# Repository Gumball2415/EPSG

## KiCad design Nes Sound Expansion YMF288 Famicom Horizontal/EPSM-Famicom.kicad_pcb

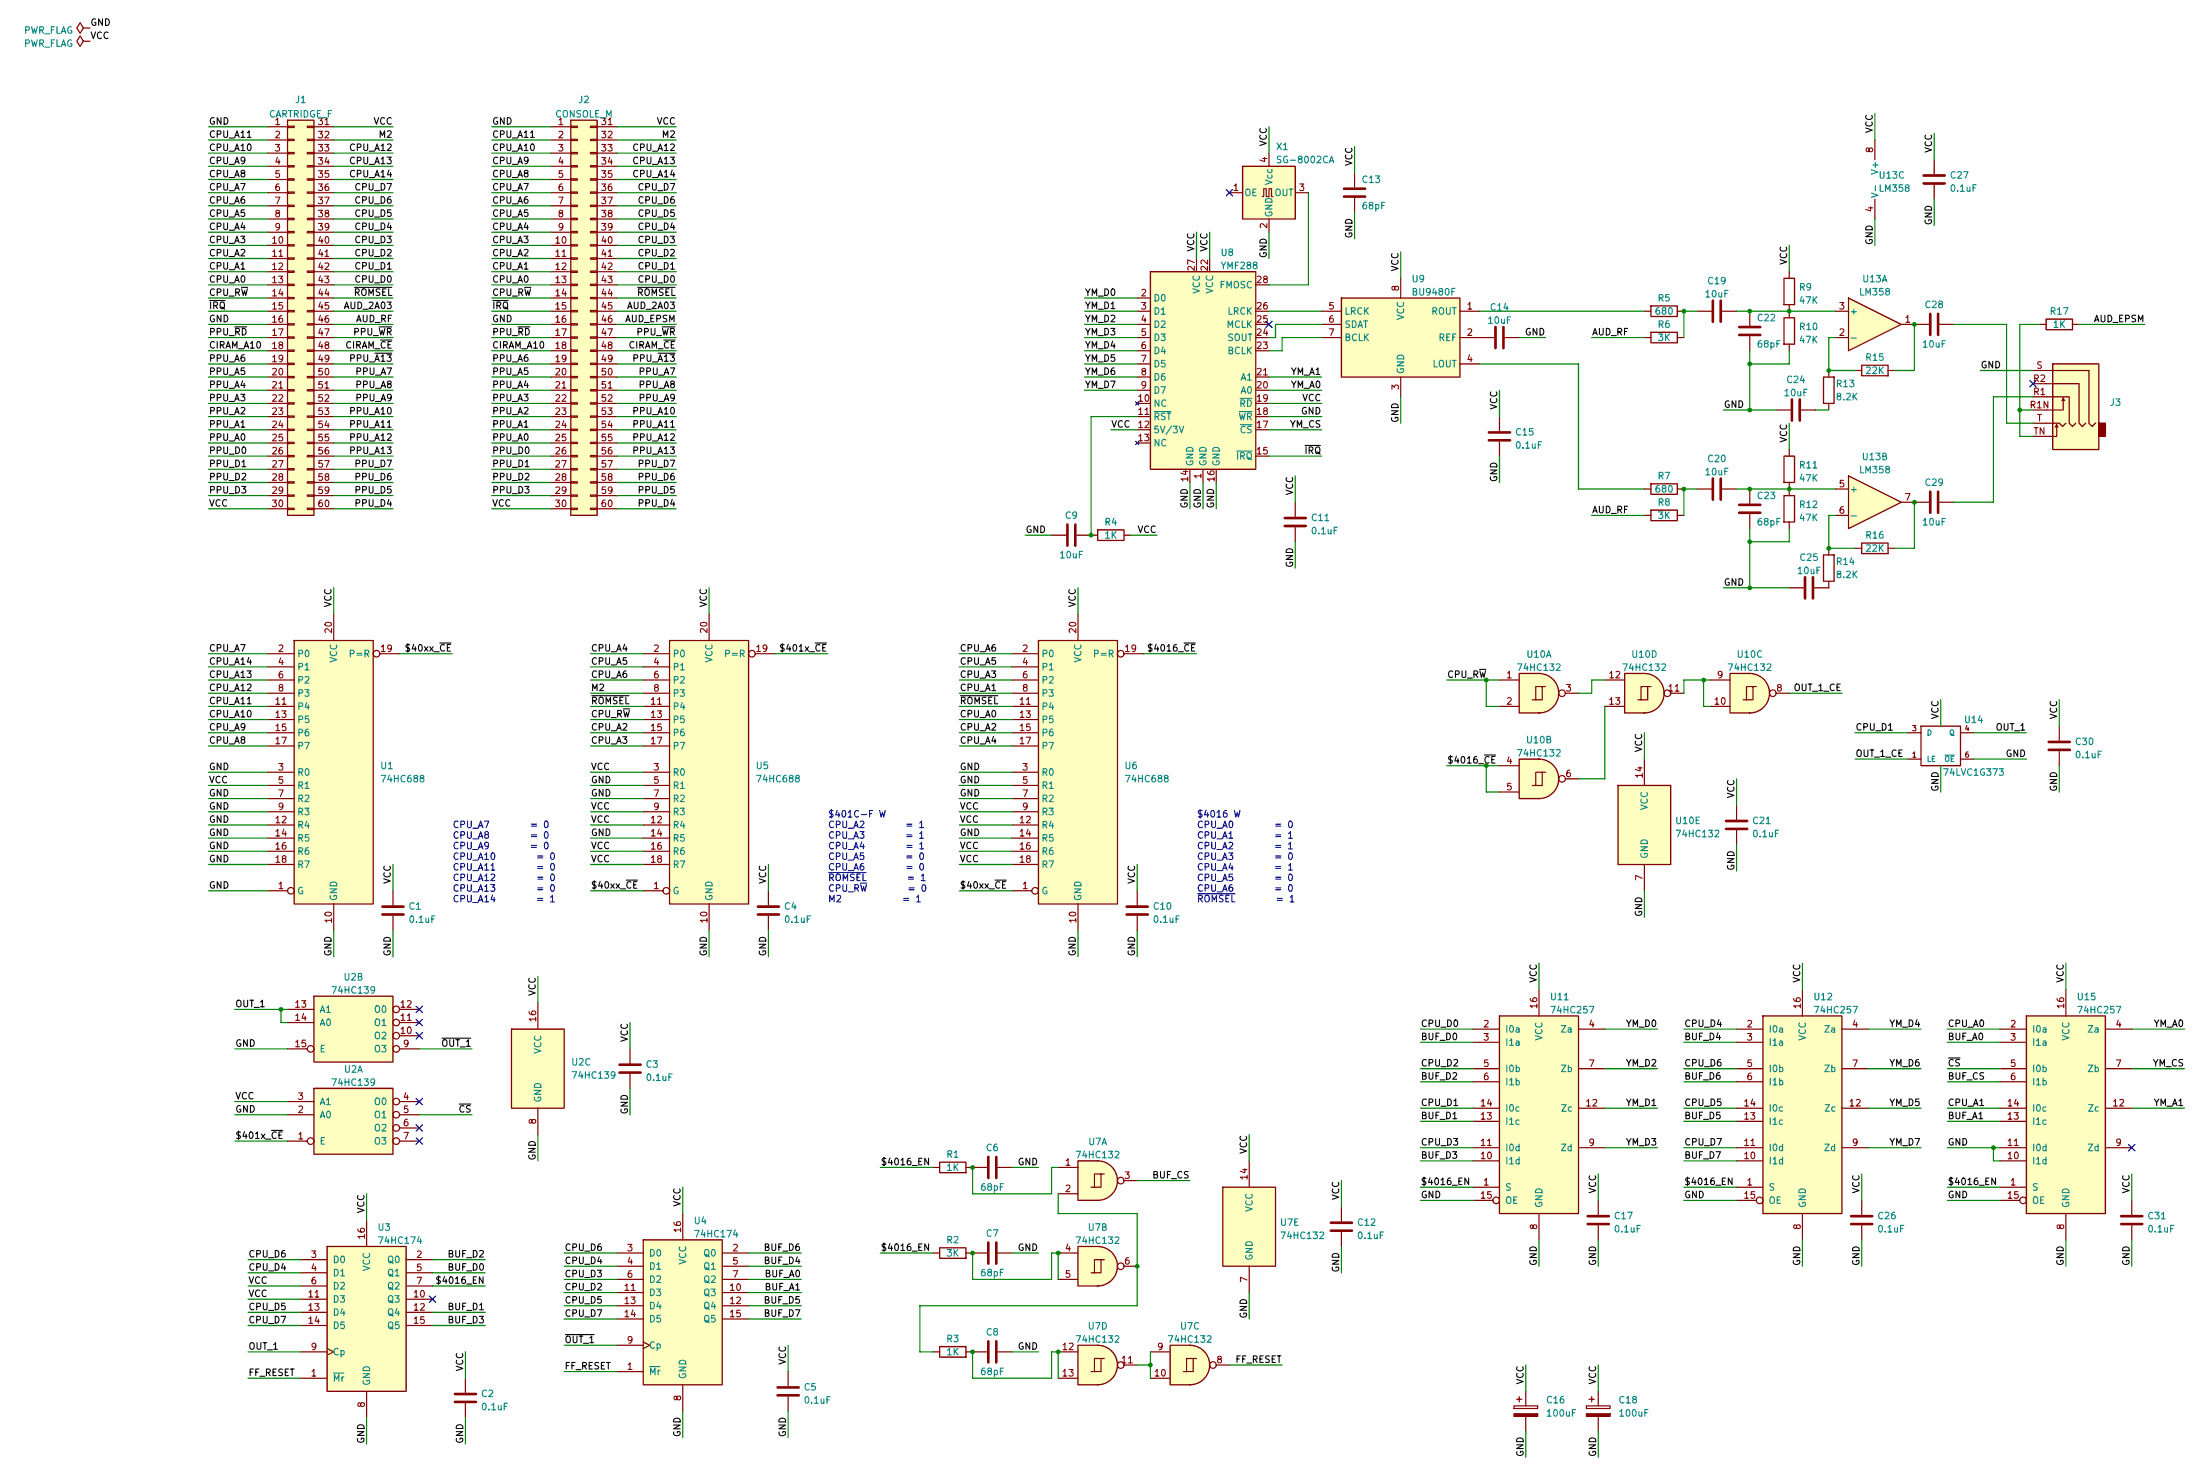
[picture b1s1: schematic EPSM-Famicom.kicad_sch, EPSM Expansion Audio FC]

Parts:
C1, C2, C3, C4, C5, C10, C11, C12, C15, C17, C21, C26, C27, C30, C31: 0.1uF; C_0805_2012Metric_Pad1.18x1.45mm_HandSolder
C6, C7, C8, C13, C22, C23: 68pF; C_0805_2012Metric_Pad1.18x1.45mm_HandSolder
C9, C14, C19, C20, C24, C25, C28, C29: 10uF; C_0805_2012Metric_Pad1.18x1.45mm_HandSolder
C16, C18: 100uF; CP_Elec_6.3x5.4
J1: CARTRIDGE_F; FC_CONN_F
J2: CONSOLE_M; HVC-ETROM-01
J3: AudioJack4_SwitchTR1; Jack_3.5mm_PJ311_Horizontal
R1, R3, R4, R17: 1K; R_0805_2012Metric_Pad1.20x1.40mm_HandSolder
R2, R6, R8: 3K; R_0805_2012Metric_Pad1.20x1.40mm_HandSolder
R5, R7: 680; R_0805_2012Metric_Pad1.20x1.40mm_HandSolder
R9, R10, R11, R12: 47K; R_0805_2012Metric_Pad1.20x1.40mm_HandSolder
R13, R14: 8.2K; R_0805_2012Metric_Pad1.20x1.40mm_HandSolder
R15, R16: 22K; R_0805_2012Metric_Pad1.20x1.40mm_HandSolder
U1, U5, U6: 74HC688; SOIC-20W_7.5x12.8mm_P1.27mm
U2: 74HC139; SOIC-16_3.9x9.9mm_P1.27mm
U3, U4: 74HC174; SOIC-16_3.9x9.9mm_P1.27mm
U7, U10: 74HC132; SOIC-14_3.9x8.7mm_P1.27mm
U8: YMF288; SOP-28_8.4x18.1mm_P1.27mm
U9: BU9480F; SOIC-8_3.9x4.9mm_P1.27mm
U11, U12, U15: 74HC257; SOIC-16_3.9x9.9mm_P1.27mm
U13: LM358; SOIC-8_3.9x4.9mm_P1.27mm
U14: 74LVC1G373; SOT-23-6
X1: SG-8002CA; Oscillator_SMD_Abracon_ASV-4Pin_7.0x5.1mm

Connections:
/$40xx_~CE: U1.19 (P=R), U5.1 (G), U6.1 (G)
/$401x_~CE: U2.1 (E), U5.19 (P=R)
/$4016_EN: R1.1, R2.1, U3.7 (Q2), U11.1 (S), U12.1 (S), U15.1 (S)
/$4016_~CE: U6.19 (P=R), U10.4, U10.5
/AUD_2A03: J1.45, J2.45
/AUD_EPSM: J2.46, R17.2
/AUD_RF: J1.46, R6.2, R8.2
/BUF_A0: U4.7 (Q2), U15.3 (I1a)
/BUF_A1: U4.10 (Q3), U15.13 (I1c)
/BUF_CS: U7.3, U15.6 (I1b)
/BUF_D0: U3.5 (Q1), U11.3 (I1a)
/BUF_D1: U3.12 (Q4), U11.13 (I1c)
/BUF_D2: U3.2 (Q0), U11.6 (I1b)
/BUF_D3: U3.15 (Q5), U11.10 (I1d)
/BUF_D4: U4.5 (Q1), U12.3 (I1a)
/BUF_D5: U4.12 (Q4), U12.13 (I1c)
/BUF_D6: U4.2 (Q0), U12.6 (I1b)
/BUF_D7: U4.15 (Q5), U12.10 (I1d)
/CIRAM_A10: J1.18, J2.18
/CIRAM_~CE: J1.48, J2.48
/CPU_A0: J1.13, J2.13, U6.13 (P5), U15.2 (I0a)
/CPU_A1: J1.12, J2.12, U6.8 (P3), U15.14 (I0c)
/CPU_A2: J1.11, J2.11, U5.15 (P6), U6.15 (P6)
/CPU_A3: J1.10, J2.10, U5.17 (P7), U6.6 (P2)
/CPU_A4: J1.9, J2.9, U5.2 (P0), U6.17 (P7)
/CPU_A5: J1.8, J2.8, U5.4 (P1), U6.4 (P1)
/CPU_A6: J1.7, J2.7, U5.6 (P2), U6.2 (P0)
/CPU_A7: J1.6, J2.6, U1.2 (P0)
/CPU_A8: J1.5, J2.5, U1.17 (P7)
/CPU_A9: J1.4, J2.4, U1.15 (P6)
/CPU_A10: J1.3, J2.3, U1.13 (P5)
/CPU_A11: J1.2, J2.2, U1.11 (P4)
/CPU_A12: J1.33, J2.33, U1.8 (P3)
/CPU_A13: J1.34, J2.34, U1.6 (P2)
/CPU_A14: J1.35, J2.35, U1.4 (P1)
/CPU_D0: J1.43, J2.43, U11.2 (I0a)
/CPU_D1: J1.42, J2.42, U11.14 (I0c), U14.3 (D)
/CPU_D2: J1.41, J2.41, U4.11 (D3), U11.5 (I0b)
/CPU_D3: J1.40, J2.40, U4.6 (D2), U11.11 (I0d)
/CPU_D4: J1.39, J2.39, U3.4 (D1), U4.4 (D1), U12.2 (I0a)
/CPU_D5: J1.38, J2.38, U3.13 (D4), U4.13 (D4), U12.14 (I0c)
/CPU_D6: J1.37, J2.37, U3.3 (D0), U4.3 (D0), U12.5 (I0b)
/CPU_D7: J1.36, J2.36, U3.14 (D5), U4.14 (D5), U12.11 (I0d)
/CPU_R~W: J1.14, J2.14, U5.13 (P5), U10.1, U10.2
/FF_RESET: U3.1 (~Mr), U4.1 (~Mr), U7.8
/M2: J1.32, J2.32, U5.8 (P3)
/OUT_1: U2.13 (A1), U2.14 (A0), U3.9 (Cp), U14.4 (Q)
/OUT_1_CE: U10.8, U14.1 (LE)
/PPU_A0: J1.25, J2.25
/PPU_A1: J1.24, J2.24
/PPU_A2: J1.23, J2.23
/PPU_A3: J1.22, J2.22
/PPU_A4: J1.21, J2.21
/PPU_A5: J1.20, J2.20
/PPU_A6: J1.19, J2.19
/PPU_A7: J1.50, J2.50
/PPU_A8: J1.51, J2.51
/PPU_A9: J1.52, J2.52
/PPU_A10: J1.53, J2.53
/PPU_A11: J1.54, J2.54
/PPU_A12: J1.55, J2.55
/PPU_A13: J1.56, J2.56
/PPU_D0: J1.26, J2.26
/PPU_D1: J1.27, J2.27
/PPU_D2: J1.28, J2.28
/PPU_D3: J1.29, J2.29
/PPU_D4: J1.60, J2.60
/PPU_D5: J1.59, J2.59
/PPU_D6: J1.58, J2.58
/PPU_D7: J1.57, J2.57
/PPU_~A13: J1.49, J2.49
/PPU_~RD: J1.17, J2.17
/PPU_~WR: J1.47, J2.47
/YM_A0: U8.20 (A0), U15.4 (Za)
/YM_A1: U8.21 (A1), U15.12 (Zc)
/YM_CS: U8.17 (~CS), U15.7 (Zb)
/YM_D0: U8.2 (D0), U11.4 (Za)
/YM_D1: U8.3 (D1), U11.12 (Zc)
/YM_D2: U8.4 (D2), U11.7 (Zb)
/YM_D3: U8.5 (D3), U11.9 (Zd)
/YM_D4: U8.6 (D4), U12.4 (Za)
/YM_D5: U8.7 (D5), U12.12 (Zc)
/YM_D6: U8.8 (D6), U12.7 (Zb)
/YM_D7: U8.9 (D7), U12.9 (Zd)
/~CS: U2.5 (O1), U15.5 (I0b)
/~IRQ: J1.15, J2.15, U8.15 (~IRQ)
/~OUT_1: U2.9 (O3), U4.9 (Cp)
/~ROMSEL: J1.44, J2.44, U5.11 (P4), U6.11 (P4)
GND: C1.1, C2.1, C3.1, C4.1, C5.1, C6.2, C7.2, C8.2, C9.1, C10.1, C11.1, C12.1, C13.2, C14.2, C15.1, C16.2, C17.1, C18.2, C21.1, C22.2, C23.2, C24.1, C25.1, C26.1, C27.1, C30.1, C31.1, J1.1, J1.16, J2.1, J2.16, J3.S, R10.2, R12.2, U1.1 (G), U1.3 (R0), U1.7 (R2), U1.9 (R3), U1.10 (GND), U1.12 (R4), U1.14 (R5), U1.16 (R6), U1.18 (R7), U2.2 (A0), U2.8 (GND), U2.15 (E), U3.8 (GND), U4.8 (GND), U5.5 (R1), U5.7 (R2), U5.10 (GND), U5.14 (R5), U6.3 (R0), U6.5 (R1), U6.7 (R2), U6.10 (GND), U6.14 (R5), U7.7 (GND), U8.1 (GND), U8.14 (GND), U8.16 (GND), U8.18 (~WR), U9.3 (GND), U10.7 (GND), U11.8 (GND), U11.15 (OE), U12.8 (GND), U12.15 (OE), U13.4 (V-), U14.2 (GND), U14.6 (~OE), U15.8 (GND), U15.10 (I1d), U15.11 (I0d), U15.15 (OE), X1.2 (GND)
unnamed: C6.1, R1.2, U7.1
unnamed: C7.1, R2.2, U7.4, U7.5
unnamed: C8.1, R3.2, U7.12, U7.13
unnamed: C9.2, R4.2, U8.11 (~RST)
unnamed: C14.1, U9.2 (REF)
unnamed: C19.1, R5.1, R6.1
unnamed: C19.2, C22.1, R9.2, R10.1, U13.3 (+)
unnamed: C20.1, R7.1, R8.1
unnamed: C20.2, C23.1, R11.2, R12.1, U13.5 (+)
unnamed: C24.2, R13.1
unnamed: C25.2, R14.1
unnamed: C28.1, R15.2, U13.1
unnamed: C28.2, J3.T
unnamed: C29.1, R16.2, U13.7
unnamed: C29.2, J3.R1
unnamed: J3.R1N, J3.TN, R17.1
unnamed: R3.1, U7.2, U7.6
unnamed: R5.2, U9.1 (ROUT)
unnamed: R7.2, U9.4 (LOUT)
unnamed: R13.2, R15.1, U13.2 (-)
unnamed: R14.2, R16.1, U13.6 (-)
unnamed: U7.9, U7.10, U7.11
unnamed: U8.23 (BCLK), U9.7 (BCLK)
unnamed: U8.24 (SOUT), U9.6 (SDAT)
unnamed: U8.26 (LRCK), U9.5 (LRCK)
unnamed: U8.28 (FMOSC), X1.3 (OUT)
unnamed: U10.9, U10.10, U10.11
unnamed: U10.3, U10.12
unnamed: U10.6, U10.13
VCC: C1.2, C2.2, C3.2, C4.2, C5.2, C10.2, C11.2, C12.2, C13.1, C15.2, C16.1, C17.2, C18.1, C21.2, C26.2, C27.2, C30.2, C31.2, J1.30, J1.31, J2.30, J2.31, R4.1, R9.1, R11.1, U1.5 (R1), U1.20 (VCC), U2.3 (A1), U2.16 (VCC), U3.6 (D2), U3.11 (D3), U3.16 (VCC), U4.16 (VCC), U5.3 (R0), U5.9 (R3), U5.12 (R4), U5.16 (R6), U5.18 (R7), U5.20 (VCC), U6.9 (R3), U6.12 (R4), U6.16 (R6), U6.18 (R7), U6.20 (VCC), U7.14 (VCC), U8.12 (5V/3V), U8.19 (~RD), U8.22 (VCC), U8.27 (VCC), U9.8 (VCC), U10.14 (VCC), U11.16 (VCC), U12.16 (VCC), U13.8 (V+), U14.5 (VCC), U15.16 (VCC), X1.4 (Vcc)

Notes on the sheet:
$4016 W CPU_A0 = 0 CPU_A1 = 1 CPU_A2 = 1 CPU_A3 = 0 CPU_A4 = 1 CPU_A5 = 0 CPU_A6 = 0 ~{ROMSEL} = 1
$401C-F W CPU_A2 = 1 CPU_A3 = 1 CPU_A4 = 1 CPU_A5 = 0 CPU_A6 = 0 ~{ROMSEL} = 1 CPU_R~{W} = 0 M2 = 1
CPU_A7 = 0 CPU_A8 = 0 CPU_A9 = 0 CPU_A10 = 0 CPU_A11 = 0 CPU_A12 = 0 CPU_A13 = 0 CPU_A14 = 1

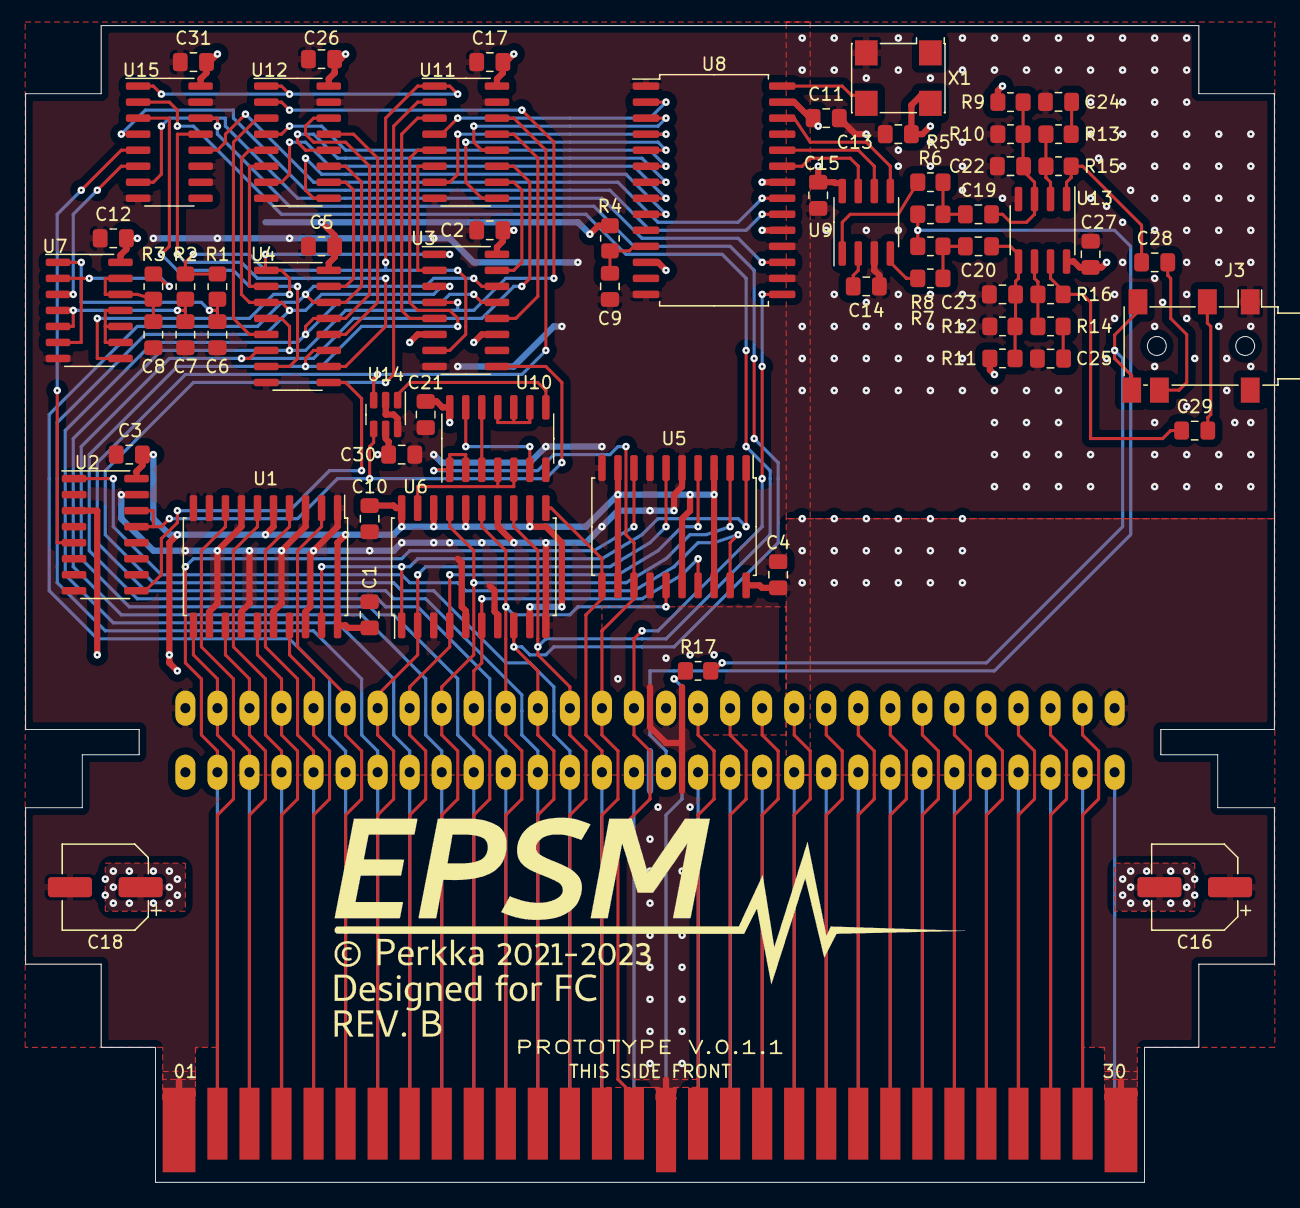
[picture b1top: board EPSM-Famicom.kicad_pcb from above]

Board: 2 copper layers, 99.0 x 91.7 mm, 68 parts (1 on the bottom side), 119 nets.

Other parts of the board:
Ref**: Val**; EPSM_silkscreen

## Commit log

2023-01-26 Fix erroneous $4016 data latch lines
2023-01-27 Fix footprint size errors
2023-01-30 Remove daughterboard connector; use two layers
2023-02-03 Improved routing
2023-03-07 Fix swapped connections
